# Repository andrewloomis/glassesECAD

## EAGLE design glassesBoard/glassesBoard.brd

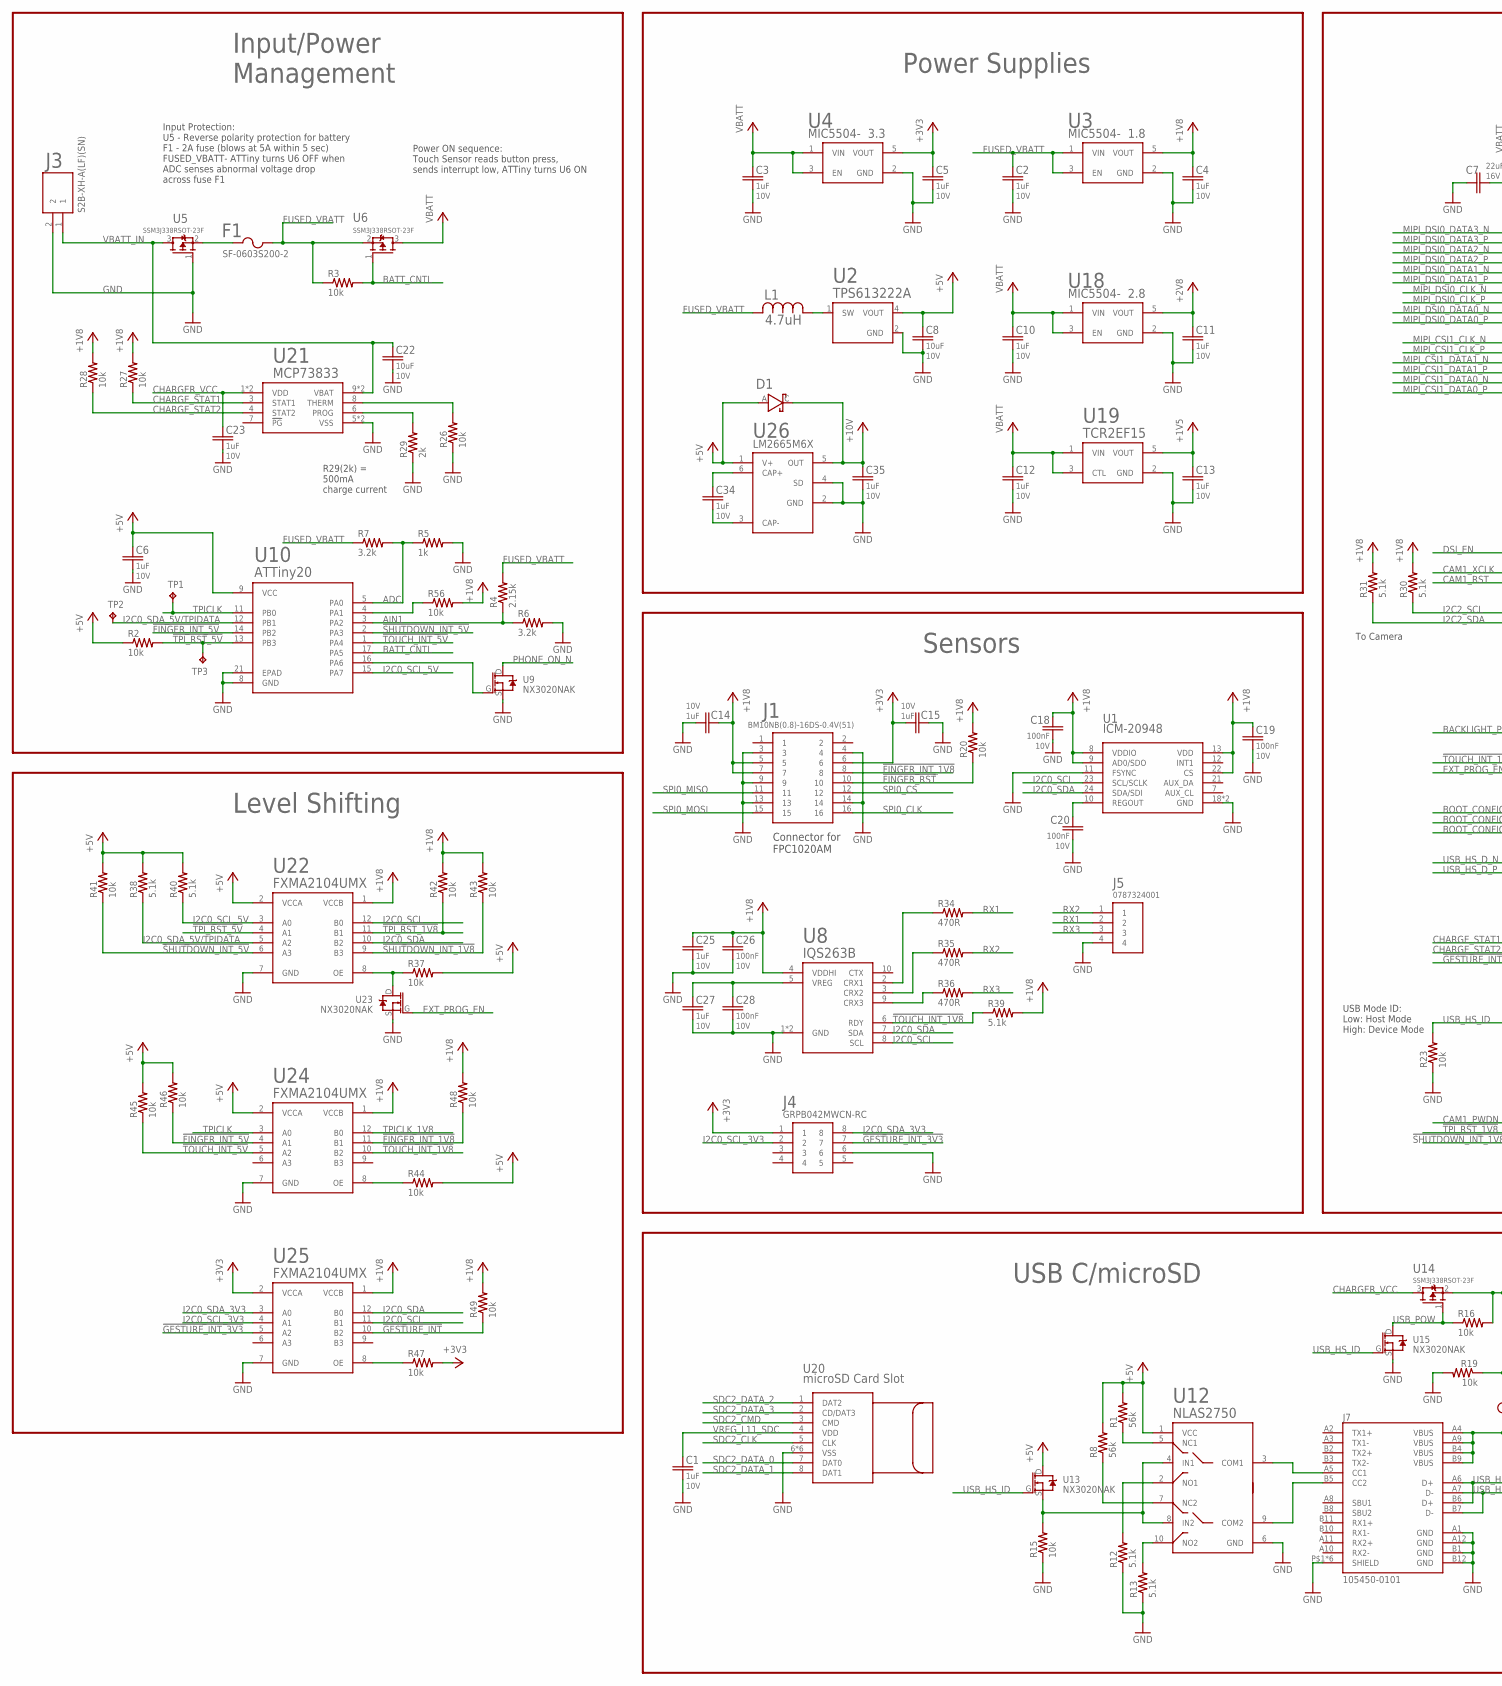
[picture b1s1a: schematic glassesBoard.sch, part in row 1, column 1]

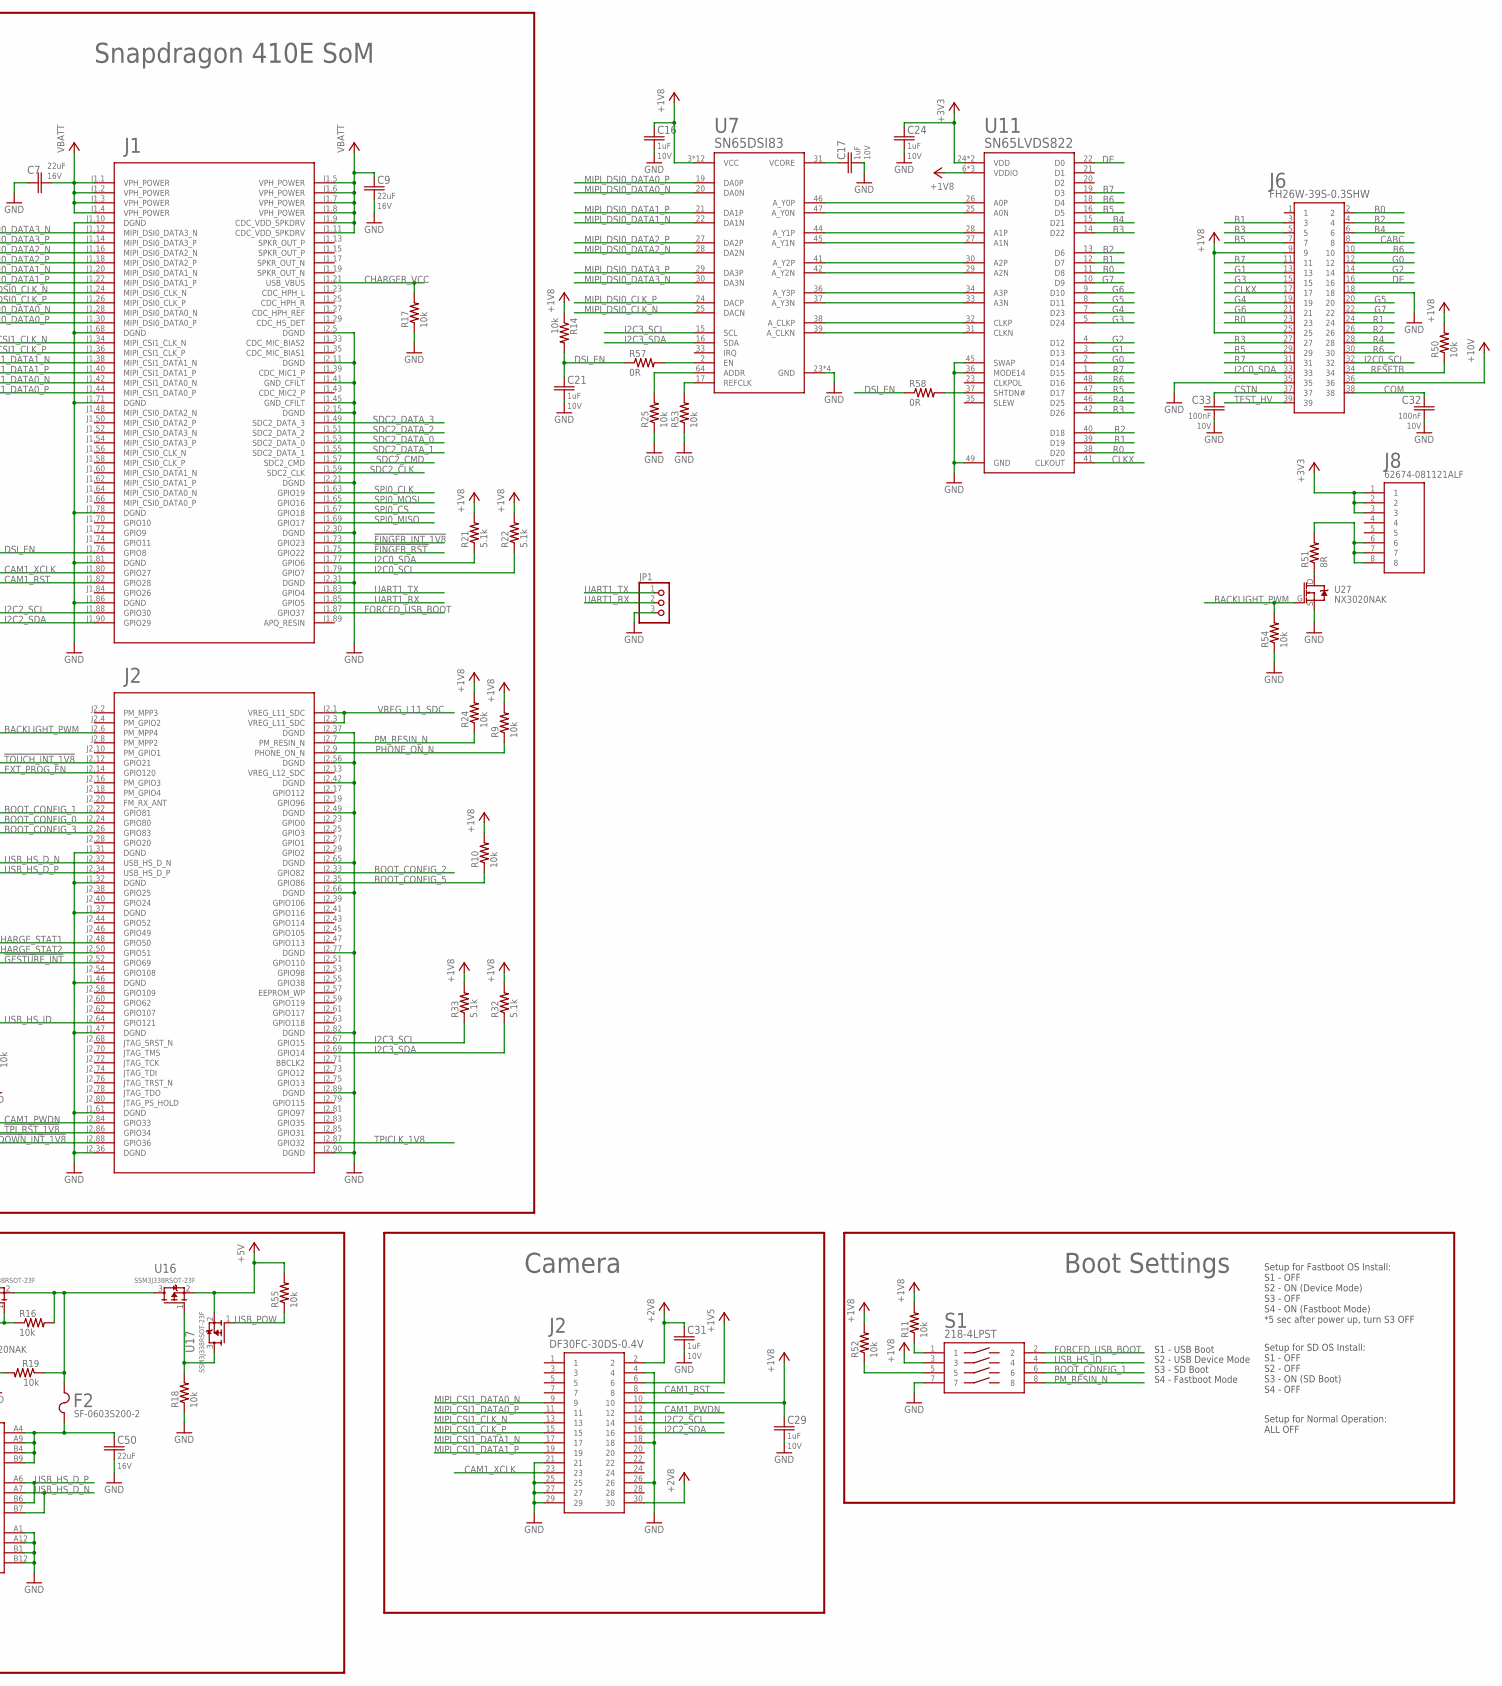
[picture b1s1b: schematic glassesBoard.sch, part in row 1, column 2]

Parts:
C1, C2, C3, C4, C5, C6, C10, C11, C12, C13, C14, C15, C16, C17, C21, C23, C24, C25, C27, C29, C31, C34, C35: 1uF; C0402
C7, C9, C50: 22uF; C0805
C8, C22: 10uF; C0603
C18, C19, C20, C26, C28, C32, C33: 100nF; C0402
D1: SDM03U40-7SC79; SOD1608X70
F1, F2: SF-0603S200-2; R0603
J1: BM10NB(0.8)-16DS-0.4V(51)
J2: DF30FC-30DS-0.4V
J3: S2B-XH-A(LF)(SN)
J4: GRPB042MWCN-RC
J5: 0787324001
J6: FH26W-39S-0.3SHW
J7: 105450-0101; MOLEX_105450-0101
J8: 62674-081121ALF
JP1: PINHD-1X3/90; 1X03/90
L1: 4.7uH; 1008
R1, R8: 56k; R0402
R2, R3, R9, R10, R11, R14, R15, R16, R17, R18, R19, R20, R23, R24, R25, R26, R27, R28, R37, R41, R42, R43, R44, R45, R46, R47, R48, R49, R50, R52, R53, R54, R55, R56: 10k; R0402
R4: 2.15k; R0402
R5: 1k; R0402
R6, R7: 3.2k; R0402
R12, R13, R21, R22, R30, R31, R32, R33, R38, R39, R40: 5.1k; R0402
R29: 2k; R0402
R34, R35, R36: 470R; R0402
R51: 8R; R0402
R57, R58: 0R; R0402
S1: 218-4LPST
TP1, TP2, TP3: TPB2,54; B2,54
U1: ICM-20948; QFN40P300X300X105-25N
U2: TPS613222A; SOT23-5
U3: 1.8; SOT23-5
U4: 3.3; SOT23-5
U5, U6, U14, U16, U17: SSM3J338RSOT-23F; SOTFL95P240X80-3
U7: SN65DSI83-Q1S-PQFP-G64; QFP50P1200X1200X120-65T300
U8: IQS263BDFN10; DFN10-3X3
U9, U13, U15, U23, U27: NX3020NAK; SOT-23_(TO-236AB)
U10: ATTINY20-MMH; 20M2
U11: SN65LVDS822VQFN48; QFN50P700X700X100-49T515
U12: NLAS2750; UQFN10
U18: 2.8; SOT23-5
U19: TCR2EF15SOT-25; SOT95P275X130-5
U20: MICROSD
U21: MCP73833; DFN10-3X3
U22, U24, U25: FXMA2104UMX; 12MLP
U26: LM2665M6XSOT23-6; SOT95P280X145-6
U$1: DART-SD410

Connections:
!FINGER_INT_1V8: J1.8, R48.1, U24.11 (B1), U$1.J1.73 (GPIO23)
!FINGER_INT_5V: R46.1, U10.14 (PB2), U24.4 (A1)
!FINGER_RST: J1.10, R20.1, U$1.J1.75 (GPIO22)
!GESTURE_INT: R49.1, U25.10 (B2), U$1.J2.52 (GPIO69)
!GESTURE_INT_3V3: J4.7, U25.5 (A2)
!SHUTDOWN_INT_1V8: R43.1, U22.9 (B3), U$1.J2.88 (GPIO36)
!SHUTDOWN_INT_5V: R41.1, U10.2 (PA3), U22.6 (A3)
!TOUCH_INT_1V8: R39.1, U8.6 (RDY), U24.10 (B2), U$1.J2.12 (GPIO21)
!TOUCH_INT_5V: R45.1, U10.1 (PA4), U24.5 (A2)
!TPI_RST_1V8: R42.1, U22.11 (B1), U$1.J2.86 (GPIO34)
!TPI_RST_5V: R2.2, TP3.TP, U10.13 (PB3), U22.4 (A1)
+1V5: C13.1, J2.6, U19.5 (VOUT)
+1V8: C4.1, C14.1, C16.1, C18.1, C19.1, C25.1, C26.1, C29.1, J1.5, J1.7, J2.10, J6.9, J6.25, R9.2, R10.2, R11.2, R14.1, R20.2, R21.2, R22.2, R24.2, R27.2, R28.2, R30.2, R31.2, R32.2, R33.2, R39.2, R42.2, R43.2, R48.2, R49.2, R50.2, R52.2, R56.2, S1.3, U1.8 (VDDIO), U1.9 (AD0/SDO), U1.13 (VDD), U1.22 (CS), U3.5 (VOUT), U7.3 (VCC), U7.14 (VCC), U7.18 (VCC), U7.32 (VCC), U7.35 (VCC), U7.40 (VCC), U7.43 (VCC), U7.48 (VCC), U7.49 (VCC), U7.55 (VCC), U7.58 (VCC), U7.63 (VCC), U8.4 (VDDHI), U11.6 (VDDIO), U11.17 (VDDIO), U11.43 (VDDIO), U22.1 (VCCB), U24.1 (VCCB), U25.1 (VCCB)
+2V8: C11.1, C31.1, J2.2, J2.30, U18.5 (VOUT)
+3V3: C5.1, C15.2, C24.1, J1.6, J4.1, J8.1, J8.2, J8.3, R47.2, U4.5 (VOUT), U11.24 (VDD), U11.44 (VDD), U25.2 (VCCA)
+5V: C6.1, C8.1, D1.A, R1.2, R2.1, R8.2, R37.2, R38.2, R40.2, R41.2, R44.2, R45.2, R46.2, R55.2, U2.4 (VOUT), U10.9 (VCC), U12.1 (VCC), U13.D, U16.2 (S), U17.2 (S), U22.2 (VCCA), U24.2 (VCCA), U26.1 (V+)
+10V: C35.1, D1.C, J6.36, U26.5 (OUT)
ADC: R5.1, R7.2, U10.5 (PA0)
AIN1: R4.1, R6.1, U10.3 (PA2)
B0: J6.2, U11.11 (D8)
B1: J6.3, U11.12 (D7)
B2: J6.4, U11.13 (D6)
B3: J6.5, U11.14 (D22)
B4: J6.6, U11.15 (D21)
B5: J6.7, U11.16 (D5)
B6: J6.10, U11.18 (D4)
B7: J6.11, U11.19 (D3)
BACKLIGHT_PWM: R54.2, U27.G, U$1.J2.6 (PM_MPP4)
BATT_CNTL: R3.2, U6.1 (G), U10.17 (PA5)
BOOT_CONFIG_0: U$1.J2.24 (GPIO80)
BOOT_CONFIG_1: S1.6, U$1.J2.22 (GPIO81)
BOOT_CONFIG_2: U$1.J2.33 (GPIO82)
BOOT_CONFIG_3: U$1.J2.26 (GPIO83)
BOOT_CONFIG_5: R10.1, U$1.J2.35 (GPIO86)
CABC: J6.8
CAM1_PWDN: J2.12, U$1.J2.84 (GPIO33)
CAM1_RST: J2.8, U$1.J1.82 (GPIO28)
CAM1_XCLK: J2.23, U$1.J1.80 (GPIO27)
CHARGER_VCC: C23.1, R17.2, U14.3 (D), U21.1 (VDD), U21.2 (VDD), U$1.J1.21 (USB_VBUS)
CHARGE_STAT1: R27.1, U21.3 (STAT1), U$1.J2.48 (GPIO50)
CHARGE_STAT2: R28.1, U21.4 (STAT2), U$1.J2.50 (GPIO51)
CLKX: J6.17, U11.41 (CLKOUT)
COM: C32.1, J6.38
CSTN: C33.1, J6.37
DE: J6.16, U11.22 (D0)
DSI_EN: C21.1, R14.2, R57.1, R58.1, U$1.J1.76 (GPIO8)
EXT_PROG_EN: U23.G, U$1.J2.14 (GPIO120)
FORCED_USB_BOOT: S1.2, U$1.J1.87 (GPIO37)
FUSED_VBATT: C2.1, F1.2, L1.P$2 (2), R3.1, R4.2, R7.1, U3.1 (VIN), U3.3 (EN), U6.2 (S)
G0: J6.12, U11.2 (D14)
G1: J6.13, U11.3 (D13)
G2: J6.14, U11.4 (D12)
G3: J6.15, U11.5 (D24)
G4: J6.19, U11.7 (D23)
G5: J6.20, U11.8 (D11)
G6: J6.21, U11.9 (D10)
G7: J6.22, U11.10 (D9)
GND: C1.2, C2.2, C3.2, C4.2, C5.2, C6.2, C7.1, C8.2, C9.2, C10.2, C11.2, C12.2, C13.2, C14.2, C15.1, C16.2, C17.2, C18.2, C19.2, C20.2, C21.2, C22.2, C23.2, C24.2, C25.2, C26.2, C27.2, C28.2, C29.2, C31.2, C32.2, C33.2, C35.2, C50.2, J1.3, J1.4, J1.9, J1.13, J1.14, J2.4, J2.18, J2.21, J2.25, J2.26, J2.27, J2.29, J3.2, J4.6, J5.4, J6.18, J6.35, J7.A1 (GND), J7.A12 (GND), J7.B1 (GND), J7.B12 (GND), J7.P$1 (SHIELD), J7.P$2 (SHIELD), J7.P$3 (SHIELD), J7.P$4 (SHIELD), J7.P$5 (SHIELD), J7.P$6 (SHIELD), JP1.3, R5.2, R6.2, R12.1, R13.1, R15.1, R17.1, R18.1, R19.2, R23.1, R25.1, R26.1, R29.1, R53.1, R54.1, S1.7, U1.11 (FSYNC), U1.18 (GND), U1.20 (GND), U2.2 (GND), U3.2 (GND), U4.2 (GND), U5.1 (G), U7.23 (GND), U7.26 (GND), U7.52 (GND), U7.65 (GND), U8.1 (GND), U8.EXP (GND), U9.S, U10.8 (GND), U10.21 (EPAD), U11.36 (MODE14), U11.45 (SWAP), U11.49 (GND), U12.6 (GND), U15.S, U18.2 (GND), U19.2 (GND), U20.6 (VSS), U20.9 (VSS), U20.10 (VSS), U20.11 (VSS), U20.12 (VSS), U20.13 (VSS), U21.5 (VSS), U21.EXP (VSS), U22.7 (GND), U23.S, U24.7 (GND), U25.7 (GND), U26.2 (GND), U26.4 (SD), U27.S, U$1.J1.10 (DGND), U$1.J1.31 (DGND), U$1.J1.32 (DGND), U$1.J1.37 (DGND), U$1.J1.41 (GND_CFILT), U$1.J1.45 (GND_CFILT), U$1.J1.46 (DGND), U$1.J1.47 (DGND), U$1.J1.61 (DGND), U$1.J1.68 (DGND), U$1.J1.71 (DGND), U$1.J1.78 (DGND), U$1.J1.81 (DGND), U$1.J1.86 (DGND), U$1.J2.5 (DGND), U$1.J2.11 (DGND), U$1.J2.15 (DGND), U$1.J2.21 (DGND), U$1.J2.30 (DGND), U$1.J2.31 (DGND), U$1.J2.36 (DGND), U$1.J2.37 (DGND), U$1.J2.42 (DGND), U$1.J2.49 (DGND), U$1.J2.56 (DGND), U$1.J2.65 (DGND), U$1.J2.66 (DGND), U$1.J2.77 (DGND), U$1.J2.82 (DGND), U$1.J2.89 (DGND), U$1.J2.90 (DGND)
I2C0_SCL: J6.32, R22.1, U1.23 (SCL/SCLK), U8.8 (SCL), U22.12 (B0), U25.11 (B1), U$1.J1.79 (GPIO7)
I2C0_SCL_3V3: J4.2, U25.4 (A1)
I2C0_SCL_5V: R40.1, U10.15 (PA7), U22.3 (A0)
I2C0_SDA: J6.33, R21.1, U1.24 (SDA/SDI), U8.7 (SDA), U22.10 (B2), U25.12 (B0), U$1.J1.77 (GPIO6)
I2C0_SDA_3V3: J4.8, U25.3 (A0)
I2C0_SDA_5V/TPIDATA: R38.1, TP2.TP, U10.12 (PB1), U22.5 (A2)
I2C2_SCL: J2.14, R30.1, U$1.J1.88 (GPIO30)
I2C2_SDA: J2.16, R31.1, U$1.J1.90 (GPIO29)
I2C3_SCL: R33.1, U7.15 (SCL), U$1.J2.67 (GPIO15)
I2C3_SDA: R32.1, U7.16 (SDA), U$1.J2.69 (GPIO14)
MIPI_CSI1_CLK_N: J2.13, U$1.J1.34 (MIPI_CSI1_CLK_N)
MIPI_CSI1_CLK_P: J2.15, U$1.J1.36 (MIPI_CSI1_CLK_P)
MIPI_CSI1_DATA0_N: J2.9, U$1.J1.42 (MIPI_CSI1_DATA0_N)
MIPI_CSI1_DATA0_P: J2.11, U$1.J1.44 (MIPI_CSI1_DATA0_P)
MIPI_CSI1_DATA1_N: J2.17, U$1.J1.38 (MIPI_CSI1_DATA1_N)
MIPI_CSI1_DATA1_P: J2.19, U$1.J1.40 (MIPI_CSI1_DATA1_P)
MIPI_DSI0_CLK_N: U7.25 (DACN), U$1.J1.24 (MIPI_DSI0_CLK_N)
MIPI_DSI0_CLK_P: U7.24 (DACP), U$1.J1.26 (MIPI_DSI0_CLK_P)
MIPI_DSI0_DATA0_N: U7.20 (DA0N), U$1.J1.28 (MIPI_DSI0_DATA0_N)
MIPI_DSI0_DATA0_P: U7.19 (DA0P), U$1.J1.30 (MIPI_DSI0_DATA0_P)
MIPI_DSI0_DATA1_N: U7.22 (DA1N), U$1.J1.20 (MIPI_DSI0_DATA1_N)
MIPI_DSI0_DATA1_P: U7.21 (DA1P), U$1.J1.22 (MIPI_DSI0_DATA1_P)
MIPI_DSI0_DATA2_N: U7.28 (DA2N), U$1.J1.16 (MIPI_DSI0_DATA2_N)
MIPI_DSI0_DATA2_P: U7.27 (DA2P), U$1.J1.18 (MIPI_DSI0_DATA2_P)
MIPI_DSI0_DATA3_N: U7.30 (DA3N), U$1.J1.12 (MIPI_DSI0_DATA3_N)
MIPI_DSI0_DATA3_P: U7.29 (DA3P), U$1.J1.14 (MIPI_DSI0_DATA3_P)
unnamed: U7.46 (A_Y0P), U11.26 (A0P)
unnamed: F1.1, U5.2 (S)
unnamed: U7.47 (A_Y0N), U11.25 (A0N)
unnamed: U7.44 (A_Y1P), U11.28 (A1P)
unnamed: U7.45 (A_Y1N), U11.27 (A1N)
unnamed: L1.P$1 (1), U2.1 (SW)
unnamed: U7.41 (A_Y2P), U11.30 (A2P)
unnamed: U7.42 (A_Y2N), U11.29 (A2N)
unnamed: U7.36 (A_Y3P), U11.34 (A3P)
unnamed: U7.37 (A_Y3N), U11.33 (A3N)
unnamed: U7.38 (A_CLKP), U11.32 (CLKP)
unnamed: U7.39 (A_CLKN), U11.31 (CLKN)
unnamed: U9.G, U10.16 (PA6)
unnamed: R11.1, S1.1
unnamed: R53.2, U7.17 (REFCLK)
unnamed: J7.B5 (CC2), U12.9 (COM2)
unnamed: J7.A5 (CC1), U12.3 (COM1)
unnamed: R13.2, U12.10 (NO2)
unnamed: R12.2, U12.2 (NO1)
unnamed: R1.1, U12.5 (NC1)
unnamed: R8.1, U12.7 (NC2)
unnamed: R15.2, U12.4 (IN1), U12.8 (IN2), U13.S
unnamed: R57.2, U7.2 (EN)
unnamed: F2.2, R16.2, R19.1, U14.2 (S), U16.3 (D)
unnamed: R18.2, U16.1 (G), U17.3 (D)
unnamed: C17.1, U7.31 (VCORE)
unnamed: R26.2, U21.8 (THERM)
unnamed: R29.2, U21.6 (PROG)
unnamed: C20.1, U1.10 (REGOUT)
unnamed: R36.1, U8.9 (CRX3)
unnamed: R35.1, U8.3 (CRX2)
unnamed: R34.1, U8.2 (CRX1)
unnamed: R37.1, U22.8 (OE), U23.D
unnamed: R52.1, S1.5
unnamed: R44.1, U24.8 (OE)
unnamed: R47.1, U25.8 (OE)
unnamed: C27.1, C28.1, U8.5 (VREG)
unnamed: C34.1, U26.6 (CAP+)
unnamed: R25.2, U7.64 (ADDR)
unnamed: C34.2, U26.3 (CAP-)
unnamed: R51.1, U27.D
unnamed: R58.2, U11.37 (SHTDN#)
unnamed: J8.6, J8.7, J8.8, R51.2
unnamed: R56.1, U10.4 (PA1)
unnamed: C50.1, F2.1, J7.A4 (VBUS), J7.A9 (VBUS), J7.B4 (VBUS), J7.B9 (VBUS)
P$1: C3.1, C7.2, C9.1, C10.1, C12.1, U4.1 (VIN), U4.3 (EN), U6.3 (D), U18.1 (VIN), U18.3 (EN), U19.1 (VIN), U19.3 (CTL), U$1.J1.1 (VPH_POWER), U$1.J1.2 (VPH_POWER), U$1.J1.3 (VPH_POWER), U$1.J1.4 (VPH_POWER), U$1.J1.5 (VPH_POWER), U$1.J1.6 (VPH_POWER), U$1.J1.7 (VPH_POWER), U$1.J1.8 (VPH_POWER), U$1.J1.9 (CDC_VDD_SPKDRV), U$1.J1.11 (CDC_VDD_SPKDRV)
PHONE_ON_N: R9.1, U9.D, U$1.J2.9 (PHONE_ON_N)
PM_RESIN_N: R24.1, S1.8, U$1.J2.7 (PM_RESIN_N)
R0: J6.23, U11.38 (D20)
R1: J6.24, U11.39 (D19)
R2: J6.26, U11.40 (D18)
R3: J6.27, U11.42 (D26)
R4: J6.28, U11.46 (D25)
R5: J6.29, U11.47 (D17)
R6: J6.30, U11.48 (D16)
R7: J6.31, U11.1 (D15)
RESETB: J6.34, R50.1
RX1: J5.2, R34.2
RX2: J5.1, R35.2
RX3: J5.3, R36.2
SDC2_CLK: U20.5 (CLK), U$1.J1.59 (SDC2_CLK)
SDC2_CMD: U20.3 (CMD), U$1.J1.57 (SDC2_CMD)
SDC2_DATA_0: U20.7 (DAT0), U$1.J1.53 (SDC2_DATA_0)
SDC2_DATA_1: U20.8 (DAT1), U$1.J1.55 (SDC2_DATA_1)
SDC2_DATA_2: U20.1 (DAT2), U$1.J1.51 (SDC2_DATA_2)
SDC2_DATA_3: U20.2 (CD/DAT3), U$1.J1.49 (SDC2_DATA_3)
SPI0_CLK: J1.16, U$1.J1.63 (GPIO19)
SPI0_CS: J1.12, U$1.J1.67 (GPIO18)
SPI0_MISO: J1.11, U$1.J1.69 (GPIO17)
SPI0_MOSI: J1.15, U$1.J1.65 (GPIO16)
TEST_HV: J6.39
TPICLK: TP1.TP, U10.11 (PB0), U24.3 (A0)
TPICLK_1V8: U24.12 (B0), U$1.J2.87 (GPIO32)
UART1_RX: JP1.2, U$1.J1.85 (GPIO5)
UART1_TX: JP1.1, U$1.J1.83 (GPIO4)
USB_HS_D_N: J7.A7 (D-), J7.B7 (D-), U$1.J2.32 (USB_HS_D_N)
USB_HS_D_P: J7.A6 (D+), J7.B6 (D+), U$1.J2.34 (USB_HS_D_P)
USB_HS_ID: R23.2, S1.4, U13.G, U15.G, U$1.J2.64 (GPIO121)
USB_POW: R16.1, R55.1, U14.1 (G), U15.D, U17.1 (G)
VBATT_IN: C22.1, J3.1, U5.3 (D), U21.9 (VBAT), U21.10 (VBAT)
VREG_L11_SDC: C1.1, U20.4 (VDD), U$1.J2.1 (VREG_L11_SDC), U$1.J2.3 (VREG_L11_SDC)

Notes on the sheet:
USB Mode ID: Low: Host Mode High: Device Mode
Power ON sequence: Touch Sensor reads button press, sends interrupt low, ATTiny turns U6 ON
Input Protection: U5 - Reverse polarity protection for battery F1 - 2A fuse (blows at 5A within 5 sec) FUSED_VBATT- ATTiny turns U6 OFF when ADC senses abnormal voltage drop across fuse F1
Power Supplies
Input/Power Management
USB C/microSD
Sensors
Camera
Snapdragon 410E SoM
To Camera
Boot Settings
S1 - USB Boot
S2 - USB Device Mode
Connector for FPC1020AM
Setup for Fastboot OS Install: S1 - OFF S2 - ON (Device Mode) S3 - OFF S4 - ON (Fastboot Mode) *5 sec after power up, turn S3 OFF
S4 - Fastboot Mode
Setup for Normal Operation: ALL OFF
R29(2k) = 500mA charge current
Level Shifting
S3 - SD Boot
Setup for SD OS Install: S1 - OFF S2 - OFF S3 - ON (SD Boot) S4 - OFF

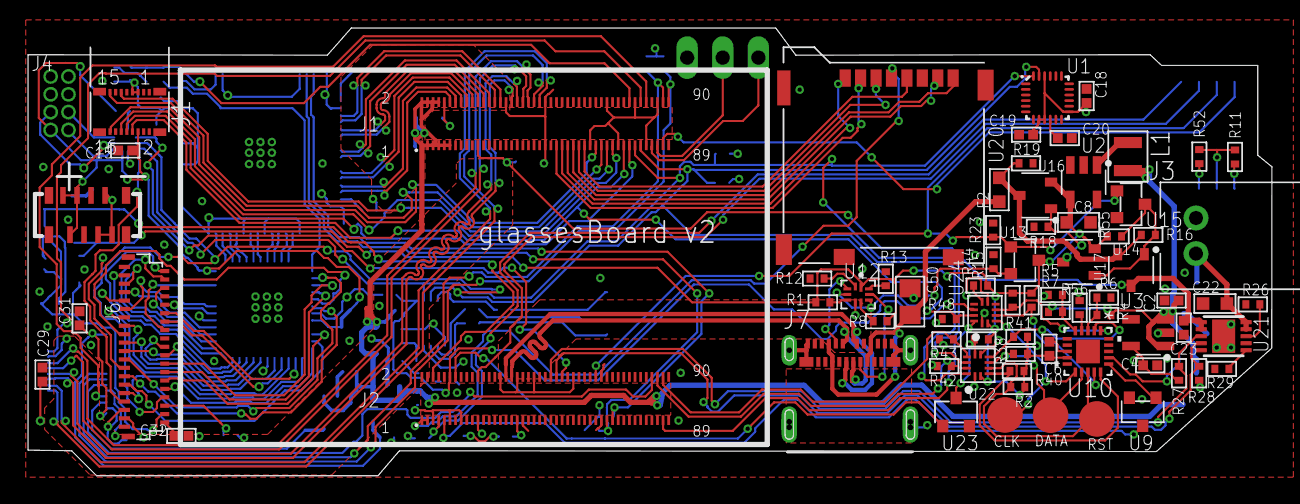
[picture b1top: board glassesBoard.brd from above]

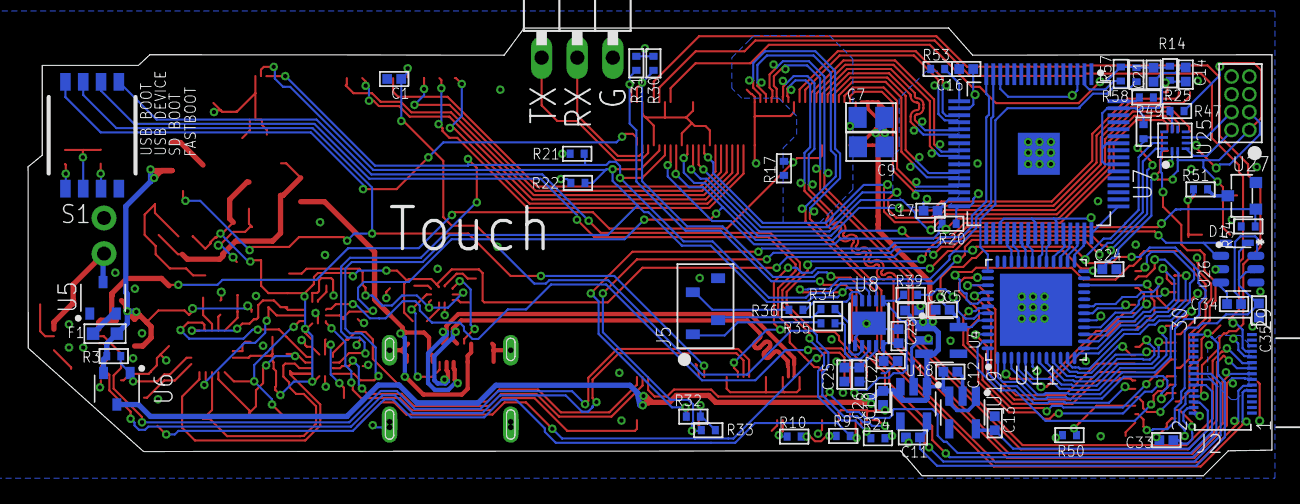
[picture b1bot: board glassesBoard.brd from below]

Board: 4 copper layers, 88.7 x 31.9 mm, 138 parts (65 on the bottom side), 160 nets.

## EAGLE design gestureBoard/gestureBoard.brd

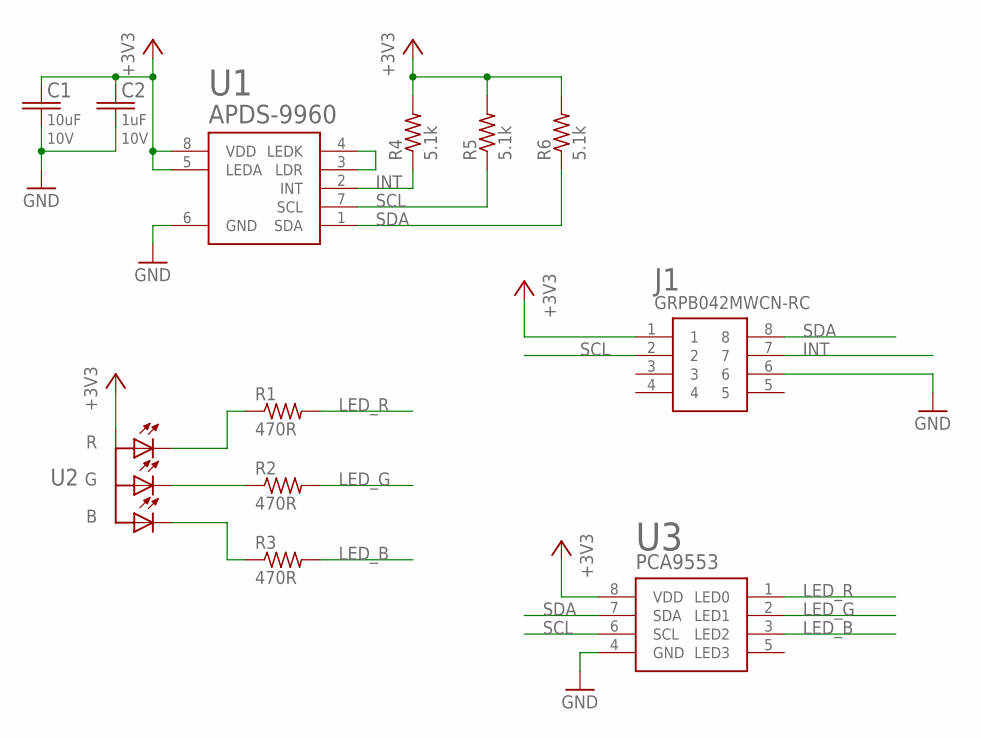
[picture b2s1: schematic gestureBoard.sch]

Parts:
C1: 10uF; C0603
C2: 1uF; C0402
J1: GRPB042MWCN-RC
R1, R2, R3: 470R; R0402
R4, R5, R6: 5.1k; R0402
U1: APDS-9960
U2: ASMB-MTB0-0A3A2; ASMB-MTB0_LED
U3: PCA9553TSSOP8; SOP65P490X110-8

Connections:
+3V3: C1.1, C2.1, J1.1, R4.2, R5.2, R6.2, U1.5 (LEDA), U1.8 (VDD), U2.1 (A), U3.8 (VDD)
GND: C1.2, C2.2, J1.6, U1.6 (GND), U3.4 (GND)
INT: J1.7, R4.1, U1.2 (INT)
LED_B: R3.2, U3.3 (LED2)
LED_G: R2.2, U3.2 (LED1)
LED_R: R1.2, U3.1 (LED0)
unnamed: R1.1, U2.4 (R)
unnamed: R2.1, U2.3 (G)
unnamed: R3.1, U2.2 (B)
unnamed: U1.3 (LDR), U1.4 (LEDK)
SCL: J1.2, R5.1, U1.7 (SCL), U3.6 (SCL)
SDA: J1.8, R6.1, U1.1 (SDA), U3.7 (SDA)

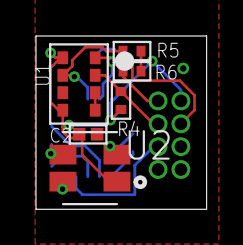
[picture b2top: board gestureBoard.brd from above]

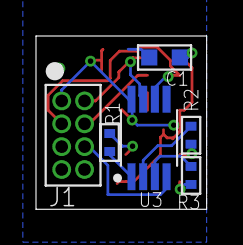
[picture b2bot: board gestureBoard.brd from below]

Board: 2 copper layers, 9.5 x 9.6 mm, 12 parts (6 on the bottom side), 12 nets.

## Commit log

2018-10-16 Started glassesBoard
2018-10-22 Added input protection design
2018-10-27 Added display converters and organized schematic
2018-10-29 Added boot select circuitry
2018-11-01 Added charger, more boot settings, more power supplies, and fingerprint sensor
2018-11-03 Started PCB component placement, made a premium service DRC
2018-11-08 Added gesture board, more level shifting and light sensor
2018-11-14 Layout almost done
2018-11-17 Removed light sensor, added serial port pins, added touch panel connector, small schematic fixes
2018-11-18 Added display connector, dip switch, 10V supply
2018-11-19 more progress on routing
2018-11-20 made more progress on routing, and added capacitive touch slider board
2018-11-20 about to move fingerprint sensor connector and add backlight connector
2018-11-21 finished rev 1 of design
2019-01-04 Fixed backwards display connector and changed backlight connector
